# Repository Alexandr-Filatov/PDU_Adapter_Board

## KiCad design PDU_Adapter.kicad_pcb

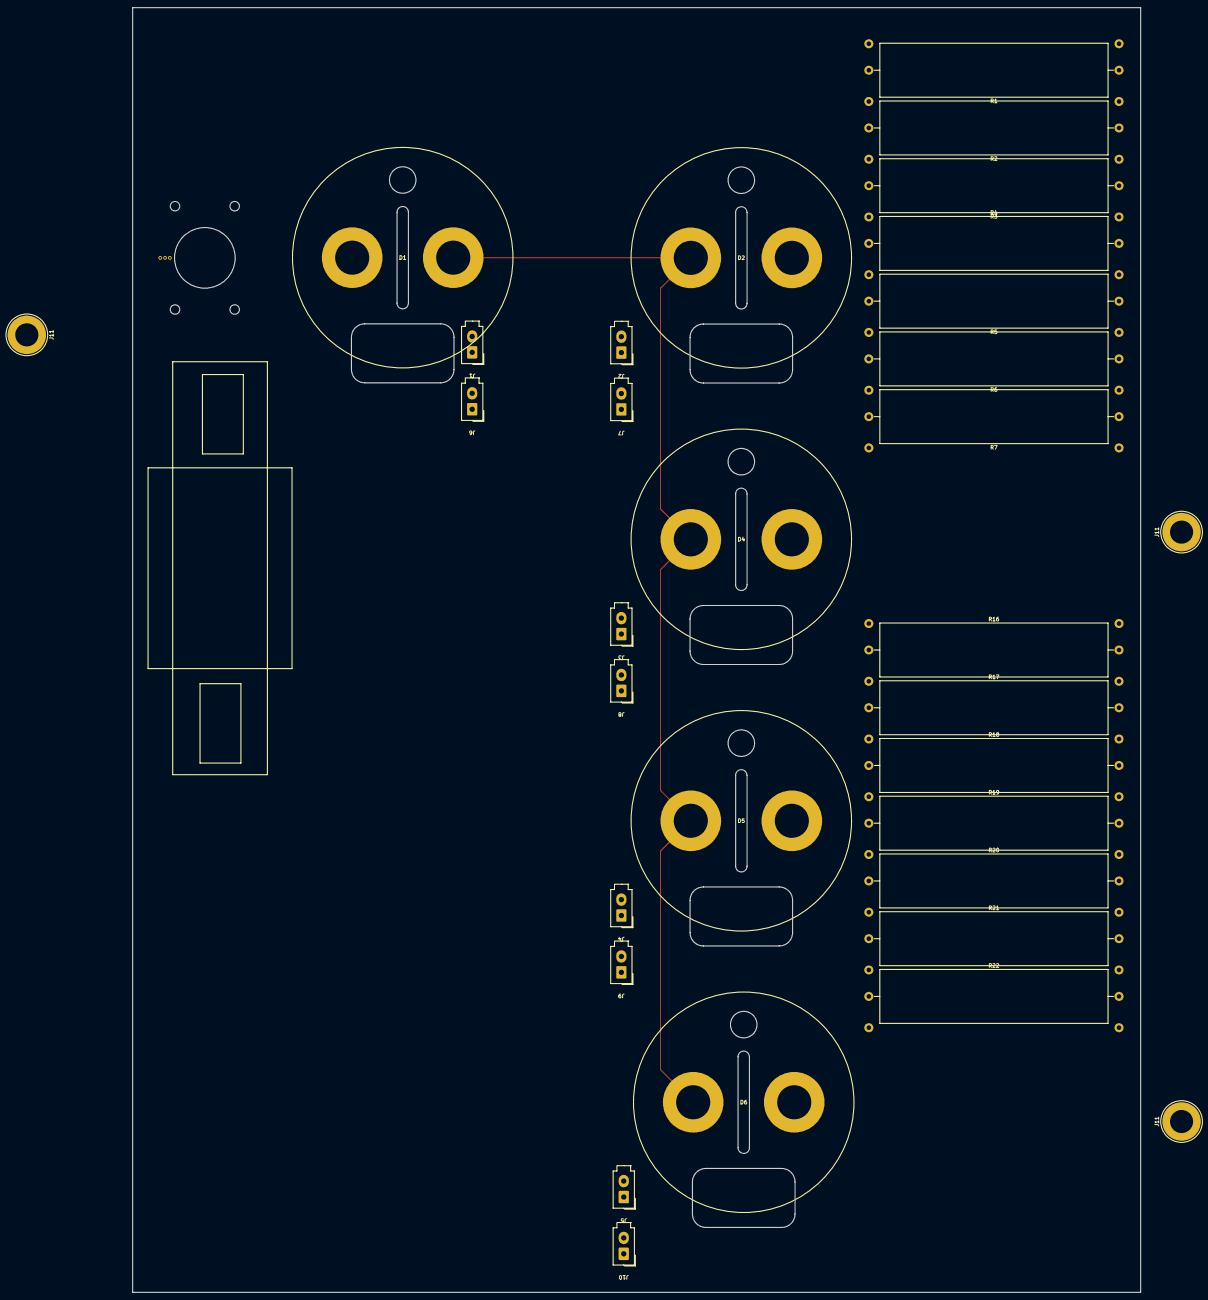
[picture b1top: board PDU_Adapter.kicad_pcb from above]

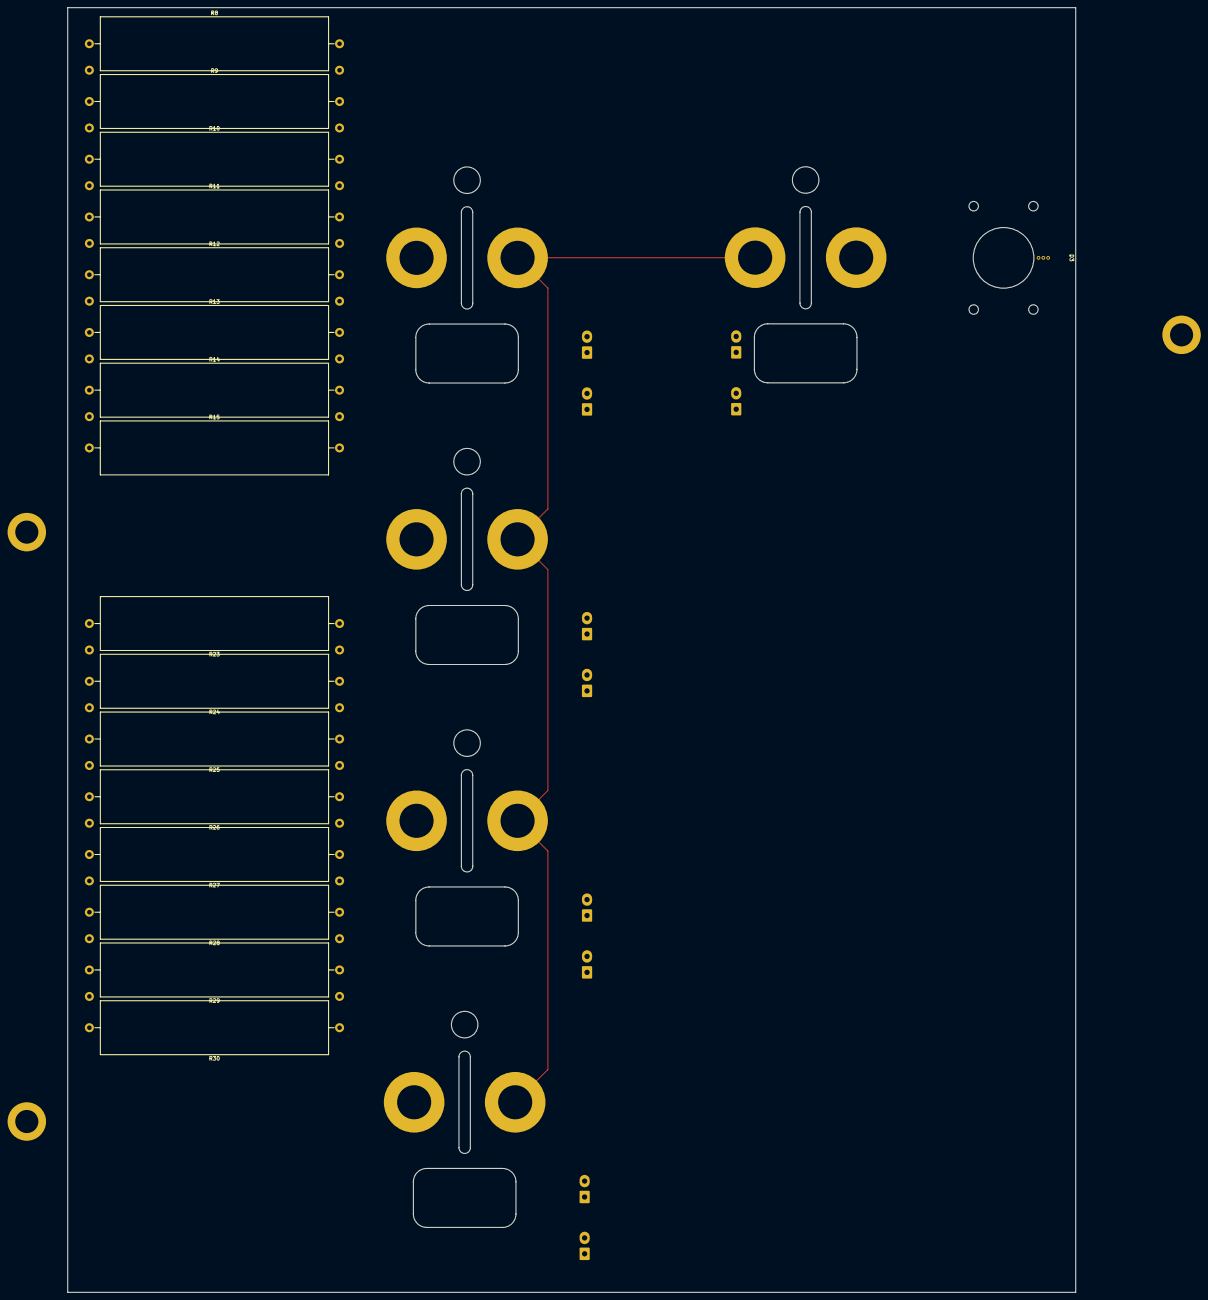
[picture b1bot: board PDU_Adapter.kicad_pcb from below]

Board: 2 copper layers, 266.1 x 339.1 mm, 49 parts (17 on the bottom side), 5 nets.

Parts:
D1, D2, D4, D5, D6: EV200
D3: YMC15S-500A
J1: Main_Contactor_Coil; Mini-Fit_01x02_Vertical
J2: Precharge_1_Coil; Mini-Fit_01x02_Vertical
J3: Shunt_1_Coil; Mini-Fit_01x02_Vertical
J4: Precharge_2_Coil; Mini-Fit_01x02_Vertical
J5: Sunt_2_Coil; Mini-Fit_01x02_Vertical
J6: Main_Contactor_FeedBack; Mini-Fit_01x02_Vertical
J7: Precharge_1_FeedBack; Mini-Fit_01x02_Vertical
J8: Shunt_1_FeedBack; Mini-Fit_01x02_Vertical
J9: Precharge_2_FeedBack; Mini-Fit_01x02_Vertical
J10: Shunt_2_FeedBack; Mini-Fit_01x02_Vertical
J11, J11#2, J11#3: Conn_01x02; Banana_Jack_1Pin
R1, R2, R3, R4, R5, R6, R7, R8, R9, R10, R11, R12, R13, R14, R15, R16, R17, R18, R19, R20, R21, R22, R23, R24, R25, R26, R27, R28, R29, R30: R; R_Axial_Power_L60.0mm_W14.0mm_P66.04mm

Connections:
unnamed: D1.A2, D2.A1, D4.A1, D5.A1, D6.A1
unnamed: D2.A2, R1.1, R2.1, R3.1, R4.1, R5.1, R6.1, R7.1, R8.1, R9.1, R10.1, R11.1, R12.1, R13.1, R14.1, R15.1
unnamed: D5.A2, R16.1, R17.1, R18.1, R19.1, R20.1, R21.1, R22.1, R23.1, R24.1, R25.1, R26.1, R27.1, R28.1, R29.1, R30.1
VDC+_ECG: D6.A2, R16.2, R17.2, R18.2, R19.2, R20.2, R21.2, R22.2, R23.2, R24.2, R25.2, R26.2, R27.2, R28.2, R29.2, R30.2
VDC+_Invertor: D4.A2, R1.2, R2.2, R3.2, R4.2, R5.2, R6.2, R7.2, R8.2, R9.2, R10.2, R11.2, R12.2, R13.2, R14.2, R15.2

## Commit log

2025-02-12 VER1.0: расставил контакторы
